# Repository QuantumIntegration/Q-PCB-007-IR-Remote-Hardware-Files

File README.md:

# Quantum DIY Kit Hardware Files - IR Remote
## Introduction

This repository contains all the hardware files necessary to build the PCBs and assemble the DIY kits. The PCBs can be ordered from for example [JLCPCB](https://jlcpcb.com/) or [PCBWay](https://www.pcbway.com/). The components can be sourced mostly from [Amazon](https://amazon.com/) or [Digikey](https://digikey.com/), according to the links in the BOM file.

## Download the correct revision

If you are nor familiar with the git version control system, please follow these simple steps to download your version of the DIY kit

<em>1. Click the branch button</em>

<em>2. Select the branch matching your revision</em>

<em>3. Click the Code button</em>

<em>4. Download the ZIP and extract it on your machine</em>

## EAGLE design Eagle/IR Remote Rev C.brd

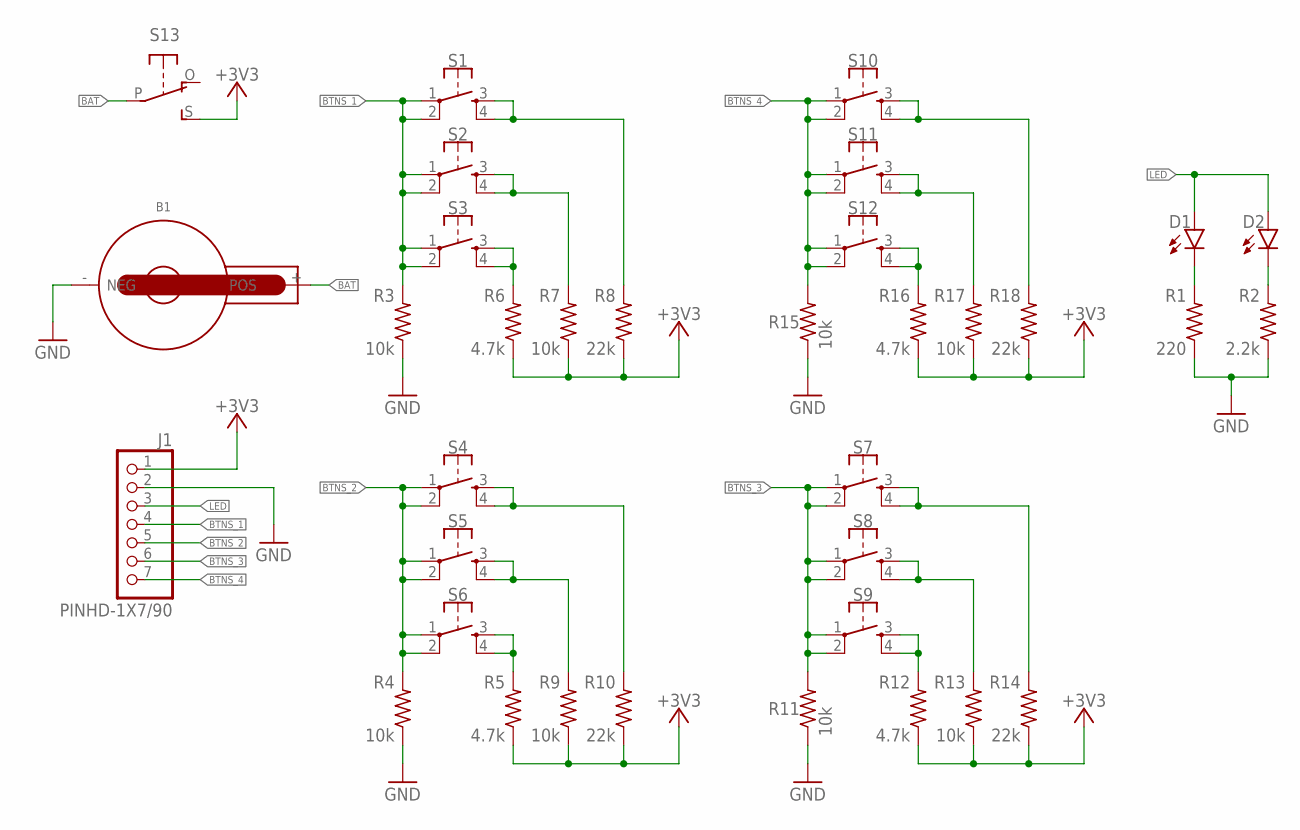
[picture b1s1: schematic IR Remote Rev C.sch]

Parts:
B1: WA-BCPH_79578211
D1, D2: LED90; LED5MM-90
J1: PINHD-1X7/90; 1X07/90
R1: 220; 0207/10
R2: 2.2k; 0207/10
R3, R4, R7, R9, R11, R13, R15, R17: 10k; 0207/10
R5, R6, R12, R16: 4.7k; 0207/10
R8, R10, R14, R18: 22k; 0207/10
S1, S2, S3, S4, S5, S6, S7, S8, S9, S10, S11, S12: TACTILE-BUTTON40XX; B3F-40XX
S13: SLIDE-SWITCHSIDE; EG1270-90

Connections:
+3V3: J1.1, R5.1, R6.1, R7.1, R8.1, R9.1, R10.1, R12.1, R13.1, R14.1, R16.1, R17.1, R18.1, S13.S
BAT: B1.+ (POS), S13.P
BTNS_1: J1.4, R3.2, S1.1, S1.2 (P1), S2.1, S2.2 (P1), S3.1, S3.2 (P1)
BTNS_2: J1.5, R4.2, S4.1, S4.2 (P1), S5.1, S5.2 (P1), S6.1, S6.2 (P1)
BTNS_3: J1.6, R11.2, S7.1, S7.2 (P1), S8.1, S8.2 (P1), S9.1, S9.2 (P1)
BTNS_4: J1.7, R15.2, S10.1, S10.2 (P1), S11.1, S11.2 (P1), S12.1, S12.2 (P1)
GND: B1.- (NEG), J1.2, R1.1, R2.1, R3.1, R4.1, R11.1, R15.1
LED: D1.A, D2.A, J1.3
unnamed: R5.2, S6.3 (S), S6.4 (S1)
unnamed: R6.2, S3.3 (S), S3.4 (S1)
unnamed: R7.2, S2.3 (S), S2.4 (S1)
unnamed: R8.2, S1.3 (S), S1.4 (S1)
unnamed: R9.2, S5.3 (S), S5.4 (S1)
unnamed: R10.2, S4.3 (S), S4.4 (S1)
unnamed: R12.2, S9.3 (S), S9.4 (S1)
unnamed: R13.2, S8.3 (S), S8.4 (S1)
unnamed: R14.2, S7.3 (S), S7.4 (S1)
unnamed: R16.2, S12.3 (S), S12.4 (S1)
unnamed: R17.2, S11.3 (S), S11.4 (S1)
unnamed: R18.2, S10.3 (S), S10.4 (S1)
unnamed: D2.K (C), R2.2
unnamed: D1.K (C), R1.2

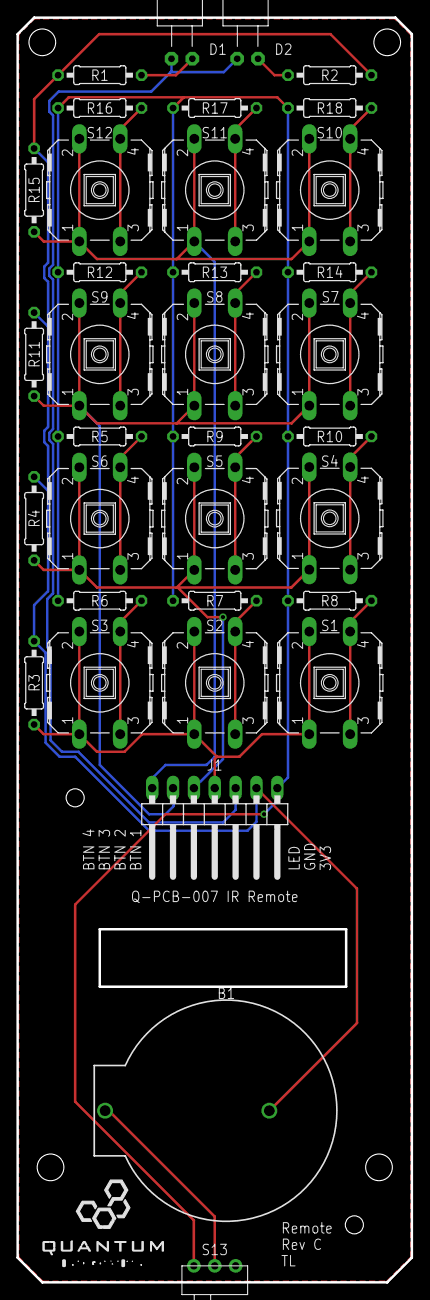
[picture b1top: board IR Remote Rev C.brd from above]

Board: 2 copper layers, 48.0 x 154.0 mm, 35 parts (0 on the bottom side), 22 nets.

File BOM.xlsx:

Index | Part | Value | Quantity | Designators | Package | Comments | Specific Part Reference | Part Link Example
1 | LED | infrared-clear | 1 | D1 | 5mm |  |  | https://www.amazon.com/Diffused-Lighting-Electronics-Compone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
2 | LED | red-clear | 1 | D2 | 5mm |  |  | https://www.amazon.com/Diffused-Lighting-Electronics-Compone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
3 | Slide Switch |  | 1 | S13 |  | 90 degree | EG1270 | https://www.digikey.com/product-detail/en/e-switch/EG1270/EG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
4 | Tactile Button |  | 12 | S1, S2, S3, S4, S5, S6, S7, S8, S9, S10, S11, S12 | B3F-40xx | black round color cap | Omron B3F-4055, Black round Cap | https://www.digikey.com/product-detail/en/omron-electronics-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
5 | Battery Holder |  | 1 | B1 |  | 2340 Battery | Würth Elektronik 79578211 | https://www.digikey.com/en/products/detail/w%C3%BCrth-elektr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
6 | Resistor | 220 | 1 | R1 | 0207/10 | 1/4 W |  | https://www.amazon.com/SIQUK-Resistors-Resistor-Assortment-E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
7 | Resistor | 2.2k | 1 | R2 | 0207/10 | 1/4 W |  | https://www.amazon.com/SIQUK-Resistors-Resistor-Assortment-E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
8 | Resistor | 4.7k | 4 | R5, R6, R12, R16 | 0207/10 | 1/4 W |  | https://www.amazon.com/SIQUK-Resistors-Resistor-Assortment-E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
9 | Resistor | 10k | 8 | R3, R4, R7, R9, R11, R13, R15, R17 | 0207/10 | 1/4 W |  | https://www.amazon.com/SIQUK-Resistors-Resistor-Assortment-E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
10 | Resistor | 22k | 4 | R8, R10, R14, R18 | 0207/10 | 1/4 W |  | https://www.amazon.com/SIQUK-Resistors-Resistor-Assortment-E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
11 | Header |  | 1 | J1 | 0.1 | 1x2, male, 90 degree, black spacers 90 degree |  | https://www.amazon.com/MCIGICM-Header-2-45mm-Arduino-Connect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
12 | M2 Standoff |  | 2 |  |  | 15mm, Female-Female |  | https://www.amazon.com/gp/product/B07CNF3W7B/ref=ppx_yo_dt_b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
13 | M2 Screw |  | 4 |  |  | 5mm |  | https://www.amazon.com/gp/product/B07CNF3W7B/ref=ppx_yo_dt_b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
14 | M3 Screw |  | 5 |  |  | 6mm |  | https://www.amazon.com/gp/product/B07CNF3W7B/ref=ppx_yo_dt_b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

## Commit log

2021-07-12 iniital commit
2021-07-12 initial content
2021-12-17 added case and schematic
2022-01-04 added arduino example

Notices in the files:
parts and their libraries:
Wurth_Assembly_WA-BCPH: Copyright: Würth Elektronik
